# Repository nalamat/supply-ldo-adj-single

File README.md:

# supply-ldo-adj-single
Low dropout adjustable single power supply based on TI TPS7A470X

Licensed under GPLv3  
Copyright 2016 NESH@NJIT

Neural Engineering of Speech and Hearing  
New Jersey Institute of Technology  
http://centers.njit.edu/nesh

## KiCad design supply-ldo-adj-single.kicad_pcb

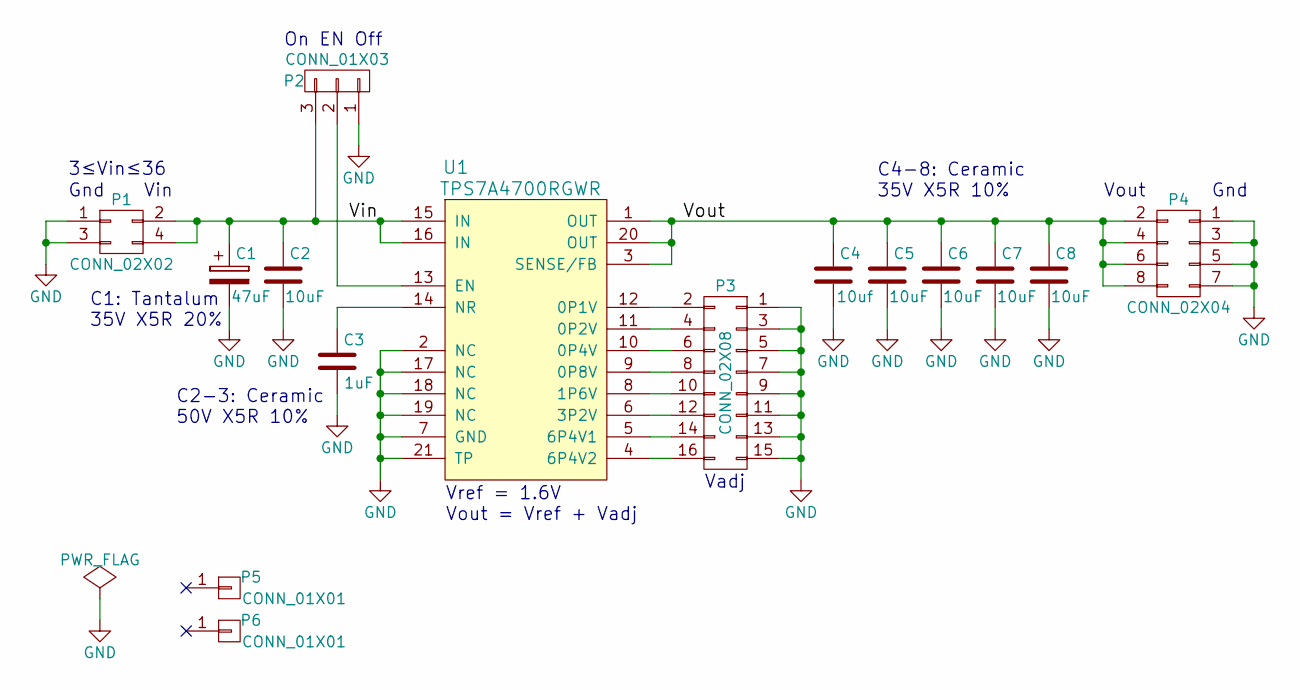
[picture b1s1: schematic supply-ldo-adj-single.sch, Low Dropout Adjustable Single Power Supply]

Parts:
C1: T495X476K035ATE300; TantalC_SizeD_EIA-7343_Reflow; Part 47uF
C2: UMK316BBJ106ML-T; C_1206; Part 10uF
C3: UMK107BJ105KA-T; C_0603; Part 1uF
C4: GRM21BR6YA106KE43L; C_0805; Part 10uf
C5, C6, C7, C8: GRM21BR6YA106KE43L; C_0805; Part 10uF
P1: CONN_02X02; Pin_Header_Straight_2x02
P2: CONN_01X03; Pin_Header_Straight_1x03
P3: CONN_02X08; Pin_Header_Straight_2x08
P4: CONN_02X04; Pin_Header_Straight_2x04
P5, P6: CONN_01X01; 1pin
U1: TPS7A4700RGWR; QFN-20-1EP_5x5mm_Pitch0.65mm

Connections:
/Vin: C1.1, C2.1, P1.2, P1.4, P2.3, U1.15 (IN), U1.16 (IN)
/Vout: C4.1, C5.1, C6.1, C7.1, C8.1, P4.2, P4.4, P4.6, P4.8, U1.1 (OUT), U1.3 (SENSE/FB), U1.20 (OUT)
GND: C1.2, C2.2, C3.2, C4.2, C5.2, C6.2, C7.2, C8.2, P1.1, P1.3, P2.1, P3.1, P3.3, P3.5, P3.7, P3.9, P3.11, P3.13, P3.15, P4.1, P4.3, P4.5, P4.7, U1.2 (NC), U1.7 (GND), U1.17 (NC), U1.18 (NC), U1.19 (NC), U1.21 (TP)
unnamed: C3.1, U1.14 (NR)
unnamed: P2.2, U1.13 (EN)
unnamed: P3.2, U1.12 (0P1V)
unnamed: P3.4, U1.11 (0P2V)
unnamed: P3.6, U1.10 (0P4V)
unnamed: P3.8, U1.9 (0P8V)
unnamed: P3.10, U1.8 (1P6V)
unnamed: P3.12, U1.6 (3P2V)
unnamed: P3.14, U1.5 (6P4V1)
unnamed: P3.16, U1.4 (6P4V2)

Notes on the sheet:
Vref = 1.6V Vout = Vref + Vadj
Vadj
Vout
Gnd
Vin
On EN Off
C4-8: Ceramic 35V X5R 10%
C1: Tantalum 35V X5R 20%
C2-3: Ceramic 50V X5R 10%
3≤Vin≤36

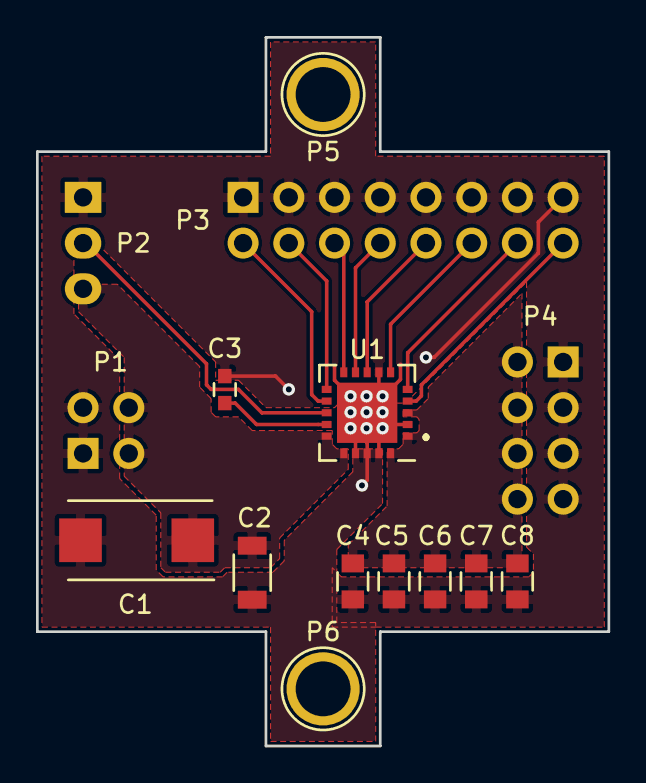
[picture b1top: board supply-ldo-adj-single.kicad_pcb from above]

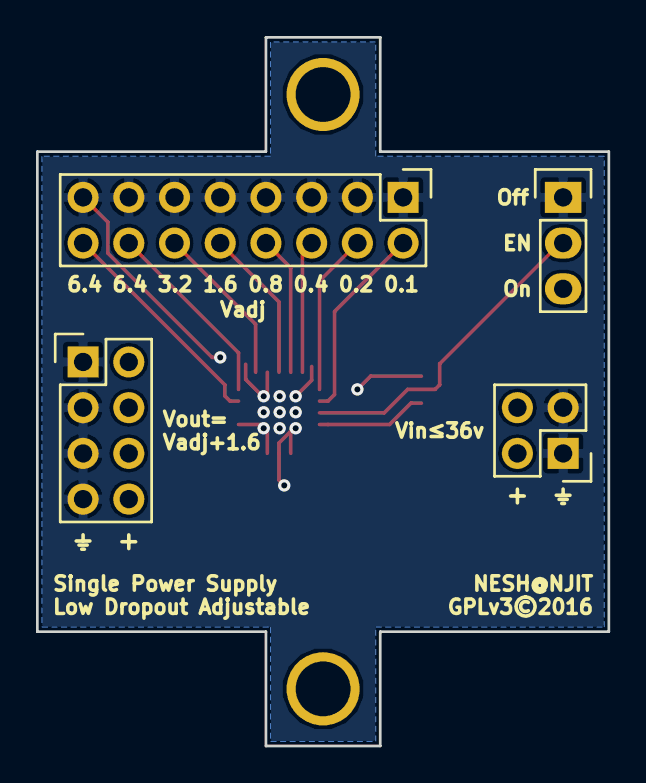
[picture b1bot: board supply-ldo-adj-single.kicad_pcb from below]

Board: 2 copper layers, 31.8 x 39.4 mm, 15 parts (4 on the bottom side), 13 nets.

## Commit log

2016-06-17 Add schematic draft
2016-06-18 Add PCB layout
2016-06-18 Add input voltage limits
2016-06-18 Cleanup
2016-06-18 Create gerber files
2016-06-18 Add license
2016-06-18 New lines
2016-06-18 Add thermal relief
2016-06-18 Update gerber files
2016-06-19 Rename LICENSE_GPLv3.md to LICENSE
2016-06-21 Reduce via size, verbose info on silkscreen
2016-06-21 Update gerber plots
2016-06-22 Increase board size, add space for heatsink
2016-06-29 Add schematic PDF
2016-06-29 Clean up
2016-08-22 Correct Vref to 1.4v

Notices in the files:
supply-ldo-adj-single.kicad_pcb:
GPLv3©2016
